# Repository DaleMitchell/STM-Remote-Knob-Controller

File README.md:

# STM Remote Knob Controller
Over the summer of 2016 I worked with the Gupta group in the Physics Research Building at The Ohio State University. While there, I applied and expanded my engineering skills by designing and building an apparatus for the remote control of a scanning tunneling microscope.

Below is a picture of the high-voltage amplifier used for controlling the probe tip of the research group’s microscope:

This is what I created:

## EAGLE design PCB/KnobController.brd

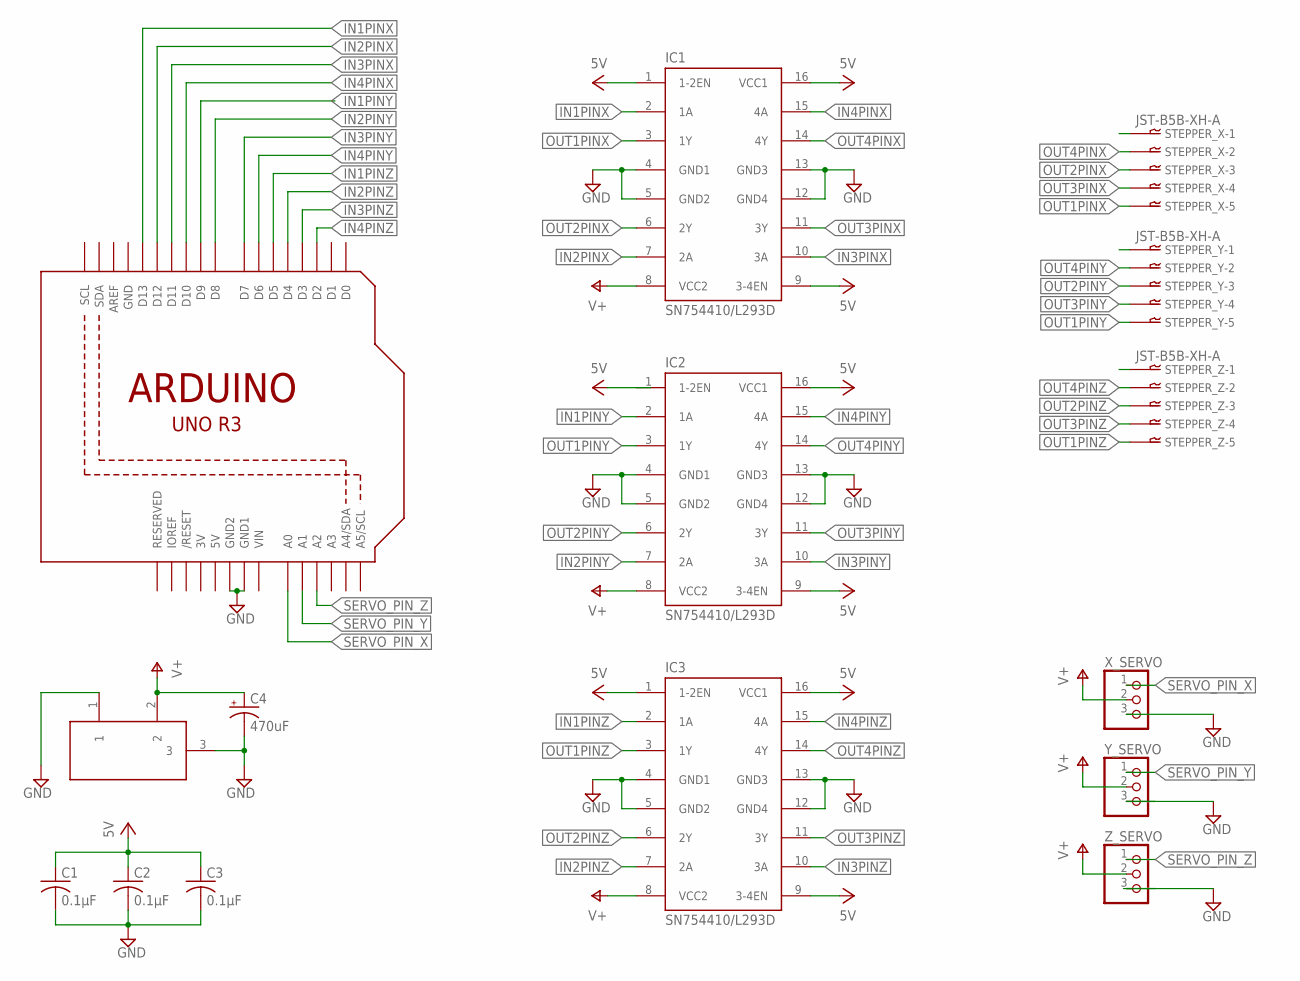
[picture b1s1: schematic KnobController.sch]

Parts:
C1, C2, C3: 0.1μF; C025-025X050
C4: 470uF; E2,5-7
IC1, IC2, IC3: SN754410/L293D; DIL16
PWR: MOTOR; DC-21MM
STEPPER_X: JST-B5B-XH-A; B5B-XH
STEPPER_Y: JST-B5B-XH-A; B5B-XH
STEPPER_Z: JST-B5B-XH-A; B5B-XH
U1: ARDUINOR3-BPLACE
X_SERVO: PINHD-1X3; 1X03
Y_SERVO: PINHD-1X3; 1X03
Z_SERVO: PINHD-1X3; 1X03

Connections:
3V: U1.3V
5V: C1.1, C2.1, C3.1, IC1.1 (1-2EN), IC1.9 (3-4EN), IC1.16 (VCC1), IC2.1 (1-2EN), IC2.9 (3-4EN), IC2.16 (VCC1), IC3.1 (1-2EN), IC3.9 (3-4EN), IC3.16 (VCC1), U1.5V
GND: C1.2, C2.2, C3.2, C4.-, IC1.4 (GND1), IC1.5 (GND2), IC1.12 (GND4), IC1.13 (GND3), IC2.4 (GND1), IC2.5 (GND2), IC2.12 (GND4), IC2.13 (GND3), IC3.4 (GND1), IC3.5 (GND2), IC3.12 (GND4), IC3.13 (GND3), PWR.1, PWR.3, U1.GND, U1.GND1, U1.GND2, X_SERVO.3, Y_SERVO.3, Z_SERVO.3
IN1PINX: IC1.2 (1A), U1.D13
IN1PINY: IC2.2 (1A), U1.D9
IN1PINZ: IC3.2 (1A), U1.D5
IN2PINX: IC1.7 (2A), U1.D12
IN2PINY: IC2.7 (2A), U1.D8
IN2PINZ: IC3.7 (2A), U1.D4
IN3PINX: IC1.10 (3A), U1.D11
IN3PINY: IC2.10 (3A), U1.D7
IN3PINZ: IC3.10 (3A), U1.D3
IN4PINX: IC1.15 (4A), U1.D10
IN4PINY: IC2.15 (4A), U1.D6
IN4PINZ: IC3.15 (4A), U1.D2
NULL: STEPPER_X.P$1
OUT1PINX: IC1.3 (1Y), STEPPER_X.P$5
OUT1PINY: IC2.3 (1Y), STEPPER_Y.P$5
OUT1PINZ: IC3.3 (1Y), STEPPER_Z.P$5
OUT2PINX: IC1.6 (2Y), STEPPER_X.P$3
OUT2PINY: IC2.6 (2Y), STEPPER_Y.P$3
OUT2PINZ: IC3.6 (2Y), STEPPER_Z.P$3
OUT3PINX: IC1.11 (3Y), STEPPER_X.P$4
OUT3PINY: IC2.11 (3Y), STEPPER_Y.P$4
OUT3PINZ: IC3.11 (3Y), STEPPER_Z.P$4
OUT4PINX: IC1.14 (4Y), STEPPER_X.P$2
OUT4PINY: IC2.14 (4Y), STEPPER_Y.P$2
OUT4PINZ: IC3.14 (4Y), STEPPER_Z.P$2
SERVO_PIN_X: U1.A0, X_SERVO.1
SERVO_PIN_Y: U1.A1, Y_SERVO.1
SERVO_PIN_Z: U1.A2, Z_SERVO.1
VCC: C4.+, IC1.8 (VCC2), IC2.8 (VCC2), IC3.8 (VCC2), PWR.2, X_SERVO.2, Y_SERVO.2, Z_SERVO.2
VIN: U1.VIN

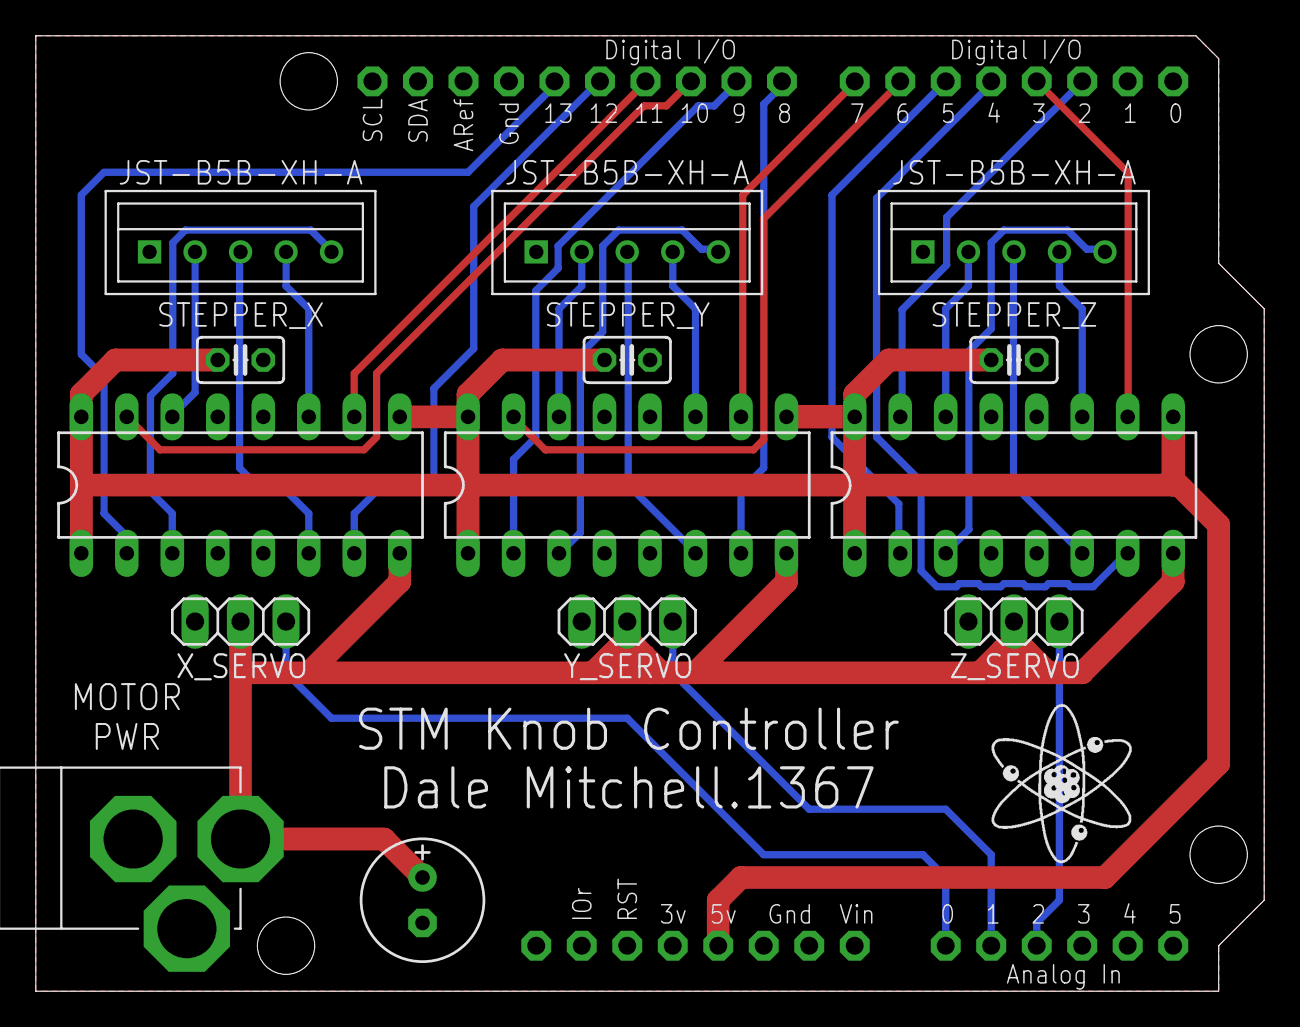
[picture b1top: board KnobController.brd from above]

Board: 2 copper layers, 68.6 x 53.3 mm, 16 parts (0 on the bottom side), 30 nets.

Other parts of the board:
U$1: ATOM

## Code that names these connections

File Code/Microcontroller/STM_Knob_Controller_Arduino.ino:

#include <Arduino.h>
#include <EEPROM.h>
#include <Servo.h>
#include <Stepper.h>

/*
 * Pin Constants
 */
//stepperX
int in1PinX = 13;
const int in2PinX = 12;
const int in3PinX = 11;
const int in4PinX = 10;

//stepperY
const int in1PinY = 9;
const int in2PinY = 8;
const int in3PinY = 7;
const int in4PinY = 6;

//stepperZ
const int in1PinZ = 5;
const int in2PinZ = 4;
const int in3PinZ = 3;
const int in4PinZ = 2;

//servos
const int servoPinX = A0;
const int servoPinY = A1;
const int servoPinZ = A2;

//Create Stepper objects.
Stepper stepperX(513, in1PinX, in2PinX, in3PinX, in4PinX);
Stepper stepperY(513, in1PinY, in2PinY, in3PinY, in4PinY);
Stepper stepperZ(513, in1PinZ, in2PinZ, in3PinZ, in4PinZ);

//Create Servo objects.
Servo servoX, servoY, servoZ;

/*
 * User input variables.
 */
//Settings for speed in RPM.
int motorSpeed = 20;

//Steps for stepper motors.
int stepsX = 0;
int stepsY = 0;
int stepsZ = 0;

//Degrees for servo motors.
int degreesX = 0;
int degreesY = 0;
int degreesZ = 0;

//Strings and chars to parse from input.
// (ex. X_G_10 = X-axis, Gain knob,    change gain to 10)
// (ex. Z_V_10 = Z-axis, Voltage knob, move 10 degrees)
String userInput = "";
char axisInput; // userInput.charAt(0);
char knobTypeInput; // userInput.charAt(2);
int stepsInput = 0; // userInput.substring(4);
int degreesInput = 0; // userInput.substring(4);

int calibrationData[][4] = { { 1, 85, 85, 90 },
							 { 3, 55, 55, 60 },
							 { 10, 25, 25, 25 },
							 { 30, 0, 0, 0 } };

//EEPROM for servos.
//int lastDegreesX = EEPROM.read(0);
//int lastDegreesY = EEPROM.read(1);
//int lastDegreesZ = EEPROM.read(2);

void setup() {
	pinMode(in1PinX, OUTPUT);
	pinMode(in2PinX, OUTPUT);
	pinMode(in3PinX, OUTPUT);
	pinMode(in4PinX, OUTPUT);

	pinMode(in1PinY, OUTPUT);
	pinMode(in2PinY, OUTPUT);
	pinMode(in3PinY, OUTPUT);
	pinMode(in4PinY, OUTPUT);

	pinMode(in1PinZ, OUTPUT);
	pinMode(in2PinZ, OUTPUT);
	pinMode(in3PinZ, OUTPUT);
	pinMode(in4PinZ, OUTPUT);

//	servoX.write(lastDegreesX);
//	servoY.write(lastDegreesY);
//	servoZ.write(lastDegreesZ);
//
//	servoX.attach(servoPinX);
//	servoY.attach(servoPinY);
//	servoZ.attach(servoPinZ);

	// wait for serial port to connect. Needed for native USB port only
	while (!Serial)
		;
	Serial.setTimeout(100);
	Serial.begin(115200);
	stepperX.setSpeed(motorSpeed);
	stepperY.setSpeed(motorSpeed);
	stepperZ.setSpeed(motorSpeed);

}

// Parsing the String
// (ex. X_V_10 = X-axis, Voltage knob, move 10 degrees)
// (ex. Z_G_10 = Z-axis, Gain knob,    change gain to 10)
// Add functionality to just change voltage according to gain (10 degrees * gain 5 = __ volts)

// V for Fine Knobs (Voltage), stepper.
// G for Clunky Knobs (Gain), servo motors.

void loop() {
	if (Serial.available()) {
		Serial.println(calibrationDataToString());
		Serial.println("Acknowledged connection!\n");
		Serial.println("The syntax to control knobs is the following:");
		Serial.println("Axis_Type_Position\n");
		Serial.println("Example command: ");
		Serial.println(
				"\"Y_V_50\"      Move voltage knob on Y axis 50 steps clockwise");
		Serial.println(
				"\"X_G_30\"      Move gain knob on X axis to the 30x position\n");
		userInput = Serial.readString();
		if (userInput.charAt(0) == 'L') {
			Serial.print(calibrationDataToString());
		} else if (userInput.charAt(0) == 'S') {
			Serial.setTimeout(3000);
			Serial.println("Ready for calibration input: ");
			String calibrationInput = Serial.readStringUntil('\n');
			calibrationDataToArray(calibrationInput);
			Serial.println("Success");
			Serial.setTimeout(50);
		} else if (userInput.length() >= 5) {
			axisInput = userInput.charAt(0);
			knobTypeInput = userInput.charAt(2);
			if (knobTypeInput == 'V') {
				stepsInput = userInput.substring(4).toInt();
				Serial.println(String(userInput.charAt(0)));
				switch (axisInput) {
				case 'X':
					stepperX.step(stepsInput);
					break;
				case 'Y':
					stepperY.step(stepsInput);
					break;
				case 'Z':
					stepperZ.step(stepsInput);
					break;
				default:
					Serial.println(
							"Input Error: Invalid axis, must be X, Y, or Z for charAt(0)");
					break;
				}
				Serial.println(
						"Moved " + String(stepsInput) + " steps on axis ");

			} else if (knobTypeInput == 'G') {
				boolean validGain = true;
				boolean validAxis = true;
				int calRow = userInput.substring(4).toInt();
				switch (calRow) {
				case 1:
					calRow = 0;
					break;
				case 3:
					calRow = 1;
					break;
				case 10:
					calRow = 2;
					break;
				case 30:
					calRow = 3;
					break;
				default:
					validGain = false;
					Serial.println(
							"Input Error: Invalid gain, must be 1, 3, 10, or 30 for substring(4)");
				}
				if (validGain) {
					int degrees = 0;
					Serial.println(String(userInput.charAt(0)));
					switch (axisInput) {
					case 'X':
						degrees = calibrationData[calRow][1];
						servoX.write(degrees);
						servoX.attach(servoPinX);
						delay(2000);
						servoX.detach();
						//EEPROM.update(0, degrees);
						break;
					case 'Y':
						degrees = calibrationData[calRow][2];
						servoX.write(degrees);
						servoX.attach(servoPinX);
						delay(2000);
						servoX.detach();
						//EEPROM.update(1, degrees);
						break;
					case 'Z':
						degrees = calibrationData[calRow][3];
						servoX.write(degrees);
						servoX.attach(servoPinX);
						delay(2000);
						servoX.detach();
						//EEPROM.update(2, degrees);
						break;
					default:
						validAxis = false;
						Serial.println(
								"Input Error: Invalid axis, must be X, Y, or Z for charAt(0)");
						break;
					}
					if (validAxis) {
						Serial.println(
								"Moved " + String(degrees) + " degrees on "
										+ axisInput + " axis ");
					}
				}

			} else {
				Serial.println(
						"Input Error: Invalid knobType, must be G or V for charAt(2)");
			}
		} else {
			Serial.println("Input Error: Does not satisfy minimum length of 5");
		}
	}
}

String calibrationDataToString(){
	int iMax = 3;
	int jMax = 3;
	String result;
	result = "[";
    for (int i = 0 ; i < 4 ; i++){
    	result += "[";
        for (int j = 0 ; j < 4 ; j++){
            result += calibrationData[i][j];
            if(j == jMax){
            	result += "]";
            } else {
            	result += ", ";
            }
        }
        if(i == iMax){
        	result += "]";
        } else {
        	result += ", ";
        }
    }
	return result;
}

void calibrationDataToArray(String input) {
    int row = 0;
    int col = 0;
    for (int i = 0; i < input.length(); i++) {
        if (input.charAt(i) == '[') {
            row++;
        }
    }
    row--;
    for (int i = 0;; i++) {
        if (input.charAt(i) == ',') {
            col++;
        }
        if (input.charAt(i) == ']') {
            break;
        }
    }
    col++;
    input.replace("\\[", "");
    input.replace("\\]", "");
    char inputArray[input.length() + 1];
    input.toCharArray(inputArray, input.length());
    Serial.println("test 1");
    char* s1 = strtok(inputArray, ", ");

    for (int i = 0, j = -1; i < input.length(); i++) {
        if (i % col == 0) {
            j++;
        }
        calibrationData[j][i % col] = s1[i];

    }
}

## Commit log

2016-10-01 first commit (images, PCB, model)
2016-10-03 upload before picture
2016-10-19 Add GUI and microcontroller code
